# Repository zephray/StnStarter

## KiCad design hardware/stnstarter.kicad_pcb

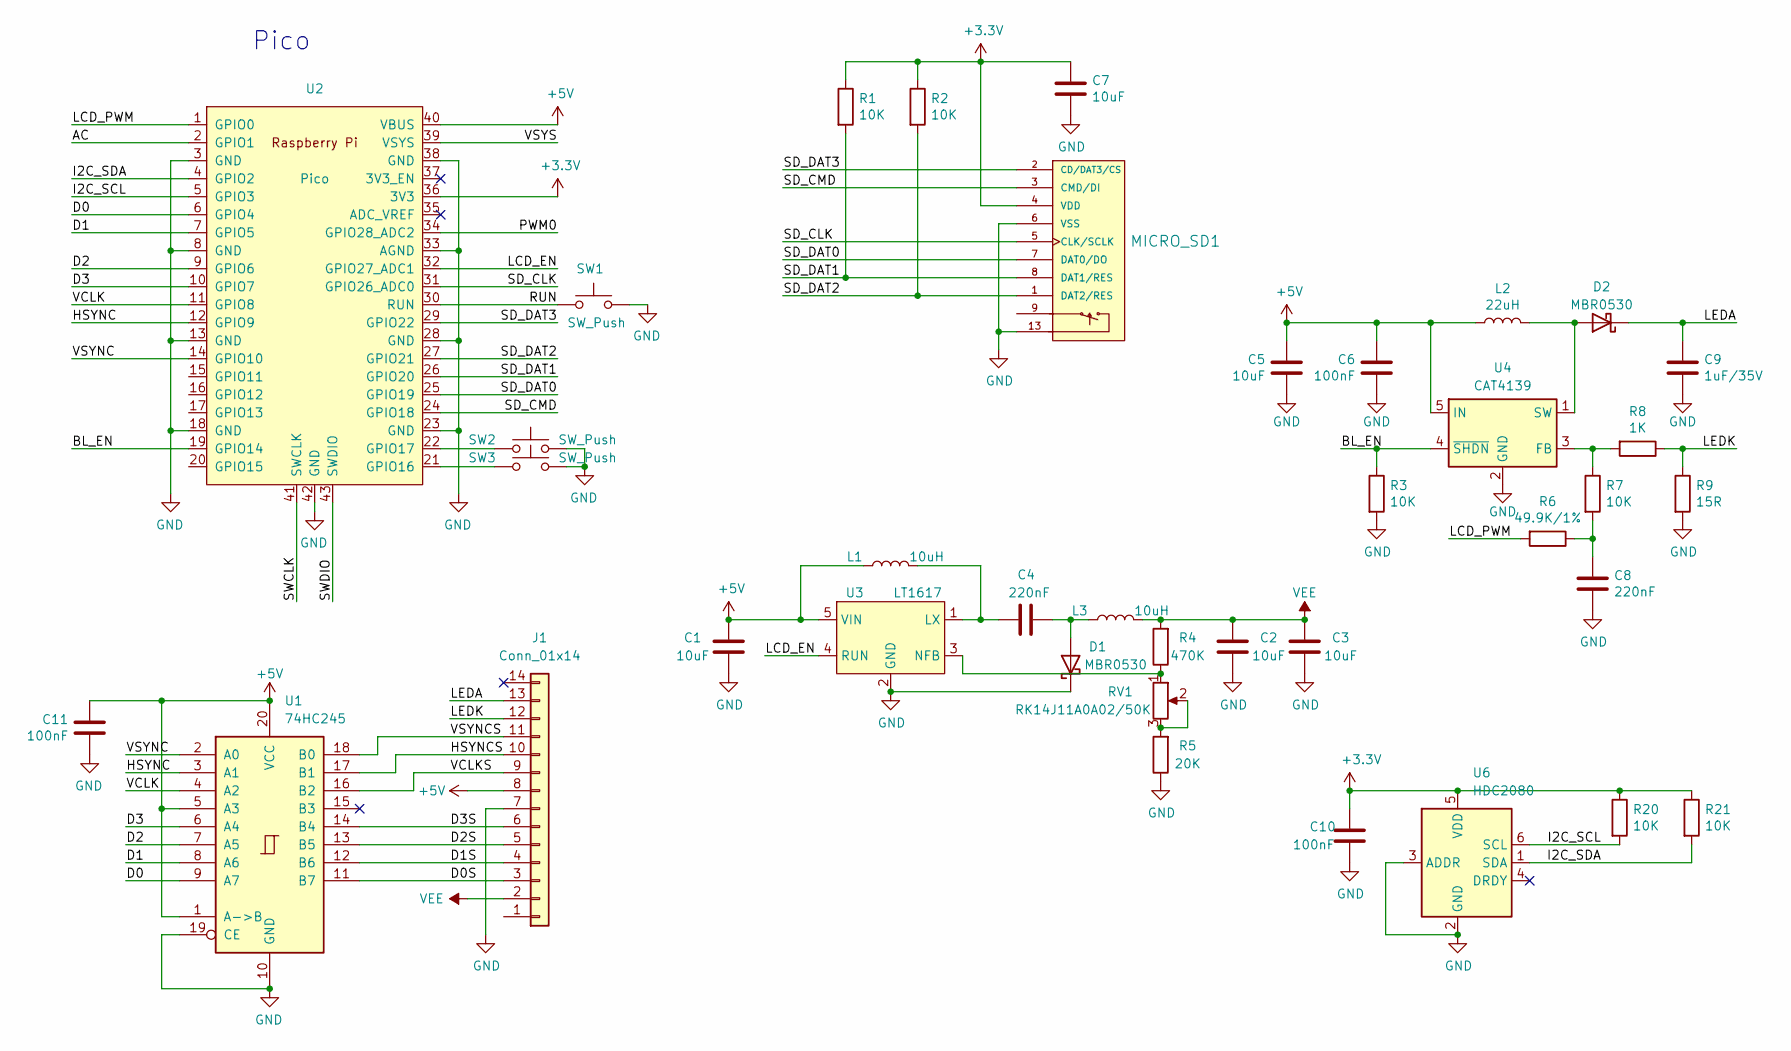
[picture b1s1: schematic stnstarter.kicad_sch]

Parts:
C1, C2, C3, C5, C7: 10uF; C_0603_1608Metric
C4, C8: 220nF; C_0402_1005Metric
C6, C10, C11: 100nF; C_0402_1005Metric
C9: 1uF/35V; C_0603_1608Metric
D1, D2: MBR0530; D_SOD-123
J1: Conn_01x14; PinSocket_1x13_P2.00mm_Vertical
L1, L3: 10uH; L_1212
L2: 22uH; L_1212
MICRO_SD1: MICRO_SD(TFC-WPAPR-08); TFC-WPAPR-08
R1, R2, R3, R7, R20, R21: 10K; R_0402_1005Metric
R4: 470K; R_0402_1005Metric
R5: 20K; R_0402_1005Metric
R6: 49.9K/1%; R_0402_1005Metric
R8: 1K; R_0402_1005Metric
R9: 15R; R_0402_1005Metric
RV1: RK14J11A0A02/50K; Potentiometer_RK14J
SW1, SW2, SW3: SW_Push; SW_SPST_CK_RS282G05A3
U1: 74HC245; WQFN-20-1EP_2.5x4.5mm_P0.5mm_EP1x2.9mm
U2: Pico; RPi_Pico_SMD_TH
U3: LT1617; SOT-23-5
U4: CAT4139; SOT-23-5
U6: HDC2080; Texas_PWSON-N6

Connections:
+3V3: C7.1, C10.2, MICRO_SD1.4 (VDD), R1.1, R2.1, R20.1, R21.1, U2.36 (3V3), U6.5 (VDD)
+5V: C1.2, C5.2, C6.2, C11.2, J1.8, L1.1, L2.1, U1.1 (A->B), U1.5 (A3), U1.20 (VCC), U2.40 (VBUS), U3.5 (VIN), U4.5 (IN)
/AC: U2.2 (GPIO1)
/BL_EN: R3.1, U2.19 (GPIO14), U4.4 (~SHDN)
/D0: U1.9 (A7), U2.6 (GPIO4)
/D0S: J1.3, U1.11 (B7)
/D1: U1.8 (A6), U2.7 (GPIO5)
/D1S: J1.4, U1.12 (B6)
/D2: U1.7 (A5), U2.9 (GPIO6)
/D2S: J1.5, U1.13 (B5)
/D3: U1.6 (A4), U2.10 (GPIO7)
/D3S: J1.6, U1.14 (B4)
/HSYNC: U1.3 (A1), U2.12 (GPIO9)
/HSYNCS: J1.10, U1.17 (B1)
/I2C_SCL: R20.2, U2.5 (GPIO3), U6.6 (SCL)
/I2C_SDA: R21.2, U2.4 (GPIO2), U6.1 (SDA)
/LCD_EN: U2.32 (GPIO27_ADC1), U3.4 (RUN)
/LCD_PWM: R6.2, U2.1 (GPIO0)
/LEDA: C9.2, D2.1 (K), J1.13
/LEDK: J1.12, R8.1, R9.1
/PWM0: U2.34 (GPIO28_ADC2)
/RUN: SW1.1, U2.30 (RUN)
/SD_CLK: MICRO_SD1.5 (CLK/SCLK), U2.31 (GPIO26_ADC0)
/SD_CMD: MICRO_SD1.3 (CMD/DI), U2.24 (GPIO18)
/SD_DAT0: MICRO_SD1.7 (DAT0/DO), U2.25 (GPIO19)
/SD_DAT1: MICRO_SD1.8 (DAT1/RES), R1.2, U2.26 (GPIO20)
/SD_DAT2: MICRO_SD1.1 (DAT2/RES), R2.2, U2.27 (GPIO21)
/SD_DAT3: MICRO_SD1.2 (CD/DAT3/CS), U2.29 (GPIO22)
/SWCLK: U2.41 (SWCLK)
/SWDIO: U2.43 (SWDIO)
/VCLK: U1.4 (A2), U2.11 (GPIO8)
/VCLKS: J1.9, U1.16 (B2)
/VSYNC: U1.2 (A0), U2.14 (GPIO10)
/VSYNCS: J1.11, U1.18 (B0)
/VSYS: U2.39 (VSYS)
GND: C1.1, C2.1, C3.1, C5.1, C6.1, C7.2, C8.1, C9.1, C10.1, C11.1, D1.1 (K), J1.7, MICRO_SD1.6 (VSS), MICRO_SD1.10, MICRO_SD1.11, MICRO_SD1.12, MICRO_SD1.13, R3.2, R5.1, R9.2, SW1.2, SW2.2, SW3.2, U1.10 (GND), U1.19 (CE), U2.3 (GND), U2.8 (GND), U2.13 (GND), U2.18 (GND), U2.23 (GND), U2.28 (GND), U2.33 (AGND), U2.38 (GND), U2.42 (GND), U3.2 (GND), U4.2 (GND), U6.2 (GND), U6.3 (ADDR)
unnamed: C8.2, R6.1, R7.2
unnamed: C4.2, D1.2 (A), L3.1
unnamed: D2.2 (A), L2.2, U4.1 (SW)
unnamed: C4.1, L1.2, U3.1 (LX)
unnamed: R4.1, RV1.1, U3.3 (NFB)
unnamed: R5.2, RV1.2, RV1.3
unnamed: R7.1, R8.2, U4.3 (FB)
unnamed: SW2.1, U2.22 (GPIO17)
unnamed: SW3.1, U2.21 (GPIO16)
VEE: C2.2, C3.2, J1.2, L3.2, R4.2

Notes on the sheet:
Pico

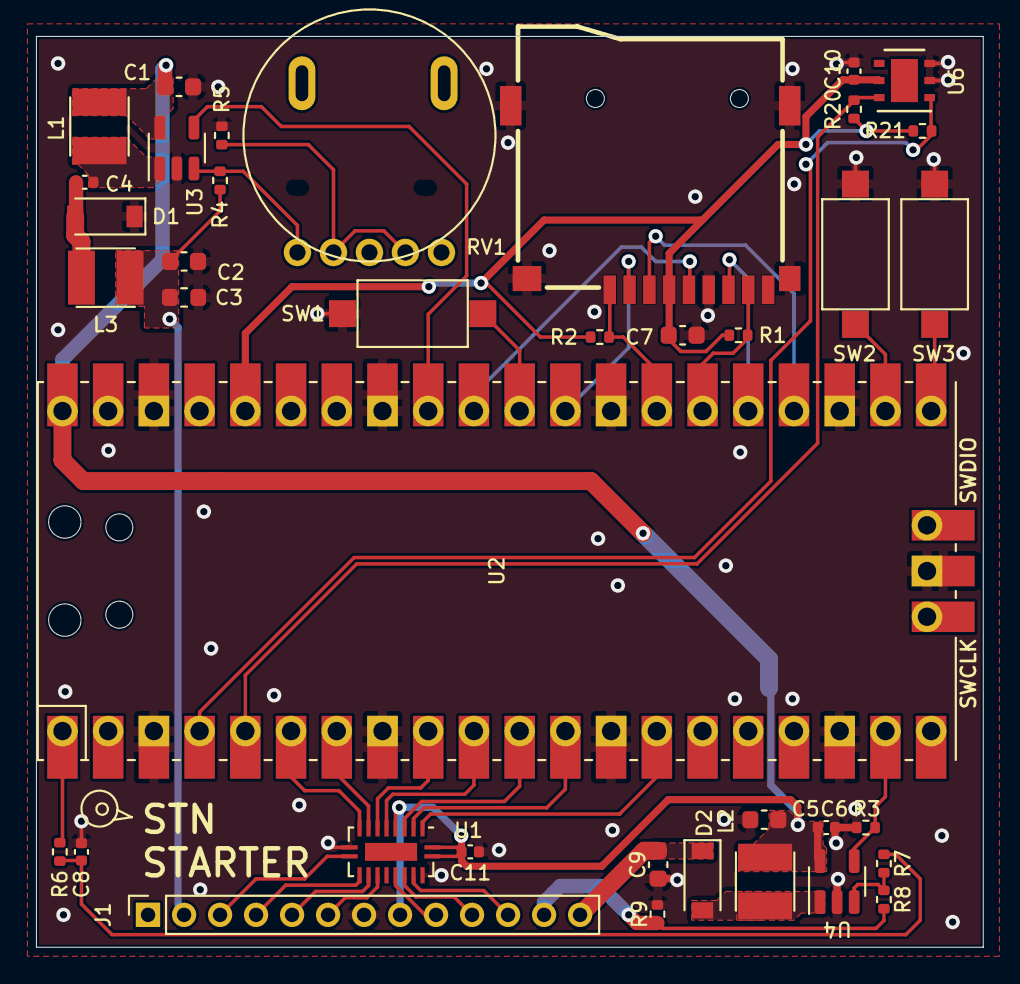
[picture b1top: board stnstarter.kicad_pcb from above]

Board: 2 copper layers, 52.6 x 50.6 mm, 38 parts (0 on the bottom side), 41 nets.

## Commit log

2022-03-09 - Initial commit
2023-01-29 Rev 0.2
